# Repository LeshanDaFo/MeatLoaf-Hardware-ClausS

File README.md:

# Meatloaf ESP32-S3 Carrier Board

Hardware designs and ready-to-flash firmware packages for the [Meatloaf](https://github.com/idolpx/meatloaf) project.

Meatloaf is an ESP32-based interface for Commodore computers. It connects to the IEC serial bus and can provide access to disk images, SD-card files, network services, and other Meatloaf firmware features.

This repository contains an independent hardware implementation designed and maintained by Claus Schlereth. The original Meatloaf firmware is developed separately in the upstream Meatloaf repository.

## Available hardware revisions

| Revision | Status | Hardware documentation | Firmware |
| --- | --- | --- | --- |
| PCB v1.0 | Published | [Documentation](Hardware/PCB-v1.0/README.md) · [KiCad files](Hardware/PCB-v1.0/KiCad/) · [Production files](Hardware/PCB-v1.0/Production/) | [Firmware packages](Firmware/v1.0/) · [Installation instructions](Firmware/README.md) |
| PCB v1.1a | Discrete IEC input stages | [Hardware package](Hardware/PCB-v1.1a/README.md) | [SPI3 firmware compatibility](Firmware/v1.1/README.md#spi3-hardware) |
| PCB v1.1b | 74LVC541A IEC input buffer | [Hardware package](Hardware/PCB-v1.1b/README.md) | [SPI3 firmware compatibility](Firmware/v1.1/README.md#spi3-hardware) |
| PCB v1.1c | USB-C power input and plug-in W5500 module | [Hardware package](Hardware/PCB-v1.1c/README.md) | [SPI3 firmware compatibility](Firmware/v1.1/README.md#spi3-hardware) |

Each hardware revision has its own design, documentation, images, and manufacturing files. Files from different revisions must not be mixed.

The table above is the starting point for revision-specific compatibility,
placement, GPIO assignments, schematics, PCB images, KiCad sources, 3D data,
and manufacturing files. The [hardware overview](Hardware/README.md) provides a
revision-independent index of the available design material.

### PCB v1.1a

PCB v1.1a uses discrete BC847BS stages for the IEC inputs.

### PCB v1.1b

PCB v1.1b replaces the discrete IEC input stages of v1.1a with a 74LVC541A
buffer and retains the BC847BS output stages.

### PCB v1.1c

PCB v1.1c adds USB-C power, a plug-in W5500 Mini module and two RGB headers.

## Getting started

### Using an assembled board

1. Identify the PCB revision and the installed ESP32 module configuration.
2. Download the matching firmware package from the appropriate [`Firmware/`](Firmware/) revision directory or from GitHub Releases.
3. Follow the [firmware installation instructions](Firmware/README.md).
4. Verify that all connections are correct before switching on the connected Commodore computer.

### Building the hardware

Before ordering or assembling a PCB:

1. Open the documentation for the required hardware revision.
2. Review its schematic and PCB layout.
3. Make sure all manufacturing files belong to the same revision.
4. Check component availability, footprints, connector orientation, and ESP32-S3 module compatibility.
5. Review the applicable license and third-party notices.

The files under `Production/` are intended for PCB manufacturing and assembly. The editable KiCad project remains the authoritative design source.

## Firmware

[Open the Meatloaf Carrier Webflasher](https://leshandafo.github.io/Meatloaf-Hardware-ClausS/) to install firmware directly from your browser.

Firmware packages are hardware-specific and may also differ by flash capacity,
PSRAM capacity, GPIO assignments, and other board configuration details. A
development-board name or matching connector position alone does not determine
the correct package.

Use the firmware link for the selected hardware revision and follow the
[`Firmware/README.md`](Firmware/README.md) instructions to identify the module
and choose a compatible package. Do not assume that firmware for one revision
or memory configuration is suitable for another.

## Repository structure

```text
.
├── Hardware/
│   ├── README.md
│   ├── PCB-v1.0/
│   │   ├── README.md
│   │   ├── 3D/
│   │   ├── Images/
│   │   ├── KiCad/
│   │   ├── PDF/
│   │   └── Production/
│   ├── PCB-v1.1a/
│   ├── PCB-v1.1b/
│   └── PCB-v1.1c/
│       ├── README.md
│       ├── 3D/
│       ├── Images/
│       ├── KiCad/
│       ├── PDF/
│       └── Production/
├── Firmware/
│   ├── README.md
│   ├── v1.0/
│   └── v1.1/
├── LICENSE.md
└── LIZENZ.md
```

Future published hardware revisions will continue to use separate directories.

## Revision history

| Date | Revision | Summary |
| --- | --- | --- |
| 2026-10-21 | PCB v1.0 | Initial published hardware revision with KiCad sources, schematic PDF, PCB images, 3D assembly, production files, and N8R8/N16R8 firmware packages |
| 2026-11-11 | PCB v1.1a, v1.1b and v1.1c | Dedicated W5500 SPI3 bus, updated KiCad projects, manufacturing files, and 3D assets |

Each hardware revision has its own technical documentation.

## Project status

This is a hobby hardware project under active development.

Features, test status, component choices, and firmware compatibility may differ between hardware revisions. Always consult the documentation for the exact PCB revision instead of assuming that information for another revision also applies.

## License and third-party materials

The original hardware design materials are provided under the project's custom non-commercial hardware license:

- [English translation](LICENSE.md)
- [Verbindliche deutsche Fassung](LIZENZ.md)

Private builds and non-profit group orders at documented actual cost are permitted under the conditions of that license. Commercial use requires separate written permission.

Firmware, KiCad libraries, component models, trademarks, and other third-party materials may be governed by separate licenses or usage conditions. The project license does not grant additional rights to those materials.

## Safety notice

The project is provided for experimentation and hobby use without a guarantee of functionality, electrical safety, regulatory compliance, or fitness for a particular purpose.

Check wiring, connector orientation, supply voltage, component ratings, and the selected hardware revision before powering the board.

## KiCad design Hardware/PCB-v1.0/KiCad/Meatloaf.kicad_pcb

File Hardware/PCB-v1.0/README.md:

# Meatloaf PCB v1.0

This document contains the assembly and connection information specific to
carrier-board revision **PCB v1.0**. Do not apply these details to another PCB
revision without checking its own documentation.

## Compatible ESP32-S3 development boards

The carrier provides one common left-hand socket row and two alternative
right-hand socket rows. It supports the following development-board layouts:

| Development-board layout | Right-hand socket row |
| --- | --- |
| [Espressif ESP32-S3-DevKitC-1](https://docs.espressif.com/projects/esp-dev-kits/en/latest/esp32s3/esp32-s3-devkitc-1/user_guide_v1.1.html) | Inner row |
| [Freenove ESP32-S3 WROOM Board](https://github.com/Freenove/Freenove_ESP32_S3_WROOM_Board) (FNK0085) | Outer row |
| [YD-ESP32-S3 development board](https://github.com/vcc-gnd/YD-ESP32-S3) | Outer row |

The firmware provided for PCB v1.0 uses the microSD-card slot on the carrier
board. Although the Freenove ESP32-S3 WROOM Board has its own microSD-card
slot, that slot is not enabled by this firmware. Insert the microSD card into
the carrier-board slot when using the Freenove board.

The socket row is determined by the board's physical dimensions, header
spacing, and pin assignment. Flash and PSRAM capacity are separate from this
mechanical choice and do not determine which socket row to use.

The named layouts are supported by this design. A different memory
variant or another board from the same product family may fit, but it is not
automatically compatible. Compare its complete pinout, header spacing, and
dimensions with the KiCad design before fitting it.

The PCB silkscreen label `ESP32-S3-DevKitC-1` identifies the development-board
layout, not its memory configuration. Determine the installed module's flash
and PSRAM capacity separately and use the
[firmware instructions](../../Firmware/README.md) to select the correct
firmware package.

## Module placement

1. Disconnect USB, IEC, and every other power source.
2. Place the carrier PCB in front of you with the two IEC connectors on the
   **left** and the status LEDs on the **right**.
3. Select the appropriate right-hand socket row:
   - Espressif ESP32-S3-DevKitC-1: **inner** right-hand socket row.
   - Freenove ESP32-S3 WROOM Board: **outer** right-hand socket row.
   - YD-ESP32-S3: **outer** right-hand socket row.
4. Orient the ESP32-S3 development board so that its USB connector or
   connectors point **downward, toward you**.
5. Carefully insert the module into the common left-hand socket row and the
   selected right-hand socket row on the component side of the carrier.
6. Check both ends of both headers. A one-pin offset will connect the wrong
   signals and may damage the module or carrier.
7. Before applying power, verify the `3V3` and `GND` positions against the
   module's own pinout.

The three placement outlines and their names are printed on the PCB
silkscreen. Fit only one ESP32-S3 board at a time; the two right-hand rows are
alternatives, not two simultaneous connections.

## GPIO usage on PCB v1.0

The following table describes the electrical connections made by the carrier
board. These assignments are taken from the current PCB v1.0 schematic and
layout.

| ESP32-S3 GPIO | Carrier-board function | Schematic net / note |
| ---: | --- | --- |
| 0 | ROOT button `SW1` | Navigates to the root directory of the internal flash filesystem |
| 1 | WiFi status LED `D2` | LED control |
| 2 | Bus status LED `D3` | LED control |
| 4 | IEC ATN | `M_ATN` |
| 5 | IEC CLK input | `M_CLK_IN` |
| 6 | IEC DATA input | `M_DATA_IN` |
| 7 | IEC SRQ | `M_SRQ` |
| 8 | IEC RESET | `M_RST` |
| 11 | microSD MOSI/CMD | `MOSI` |
| 12 | microSD clock | `SCK` |
| 13 | microSD MISO/DAT0 | `MISO` |
| 16 | IEC DATA output | `M_DATA_OUT` |
| 17 | IEC CLK output | `M_CLK_OUT` |
| 46 | microSD chip select | `CS` |

The carrier also connects the module's `3V3` and `GND` pins. The module's
`5V` and `EN`/`CHIP_PU` pins are not connected by PCB v1.0.

IEC CLK and DATA use **separate input and output GPIOs** on this carrier:
GPIO5/GPIO17 for CLK and GPIO6/GPIO16 for DATA. Firmware for PCB v1.0 must use
this split-line arrangement. A generic pin map that assigns both directions to
GPIO5 or both directions to GPIO6 does not match the carrier hardware.

GPIOs not listed above are not connected by the carrier, but they are not
necessarily free for arbitrary use: an installed development board may use
them for its own RGB LED, USB interface, camera connector, or other onboard
hardware. Do not enable a module-local peripheral if it drives a GPIO used in
the table above.

## Firmware selection

Firmware selection depends on the installed module's flash and PSRAM capacity
and must also match the carrier board's GPIO assignments and hardware
configuration. The development-board manufacturer and socket-row position
alone do not determine the correct firmware variant. Refer to the
[firmware instructions](../../Firmware/README.md) before flashing.

## Design and production files

- [Schematic PDF](PDF/Meatloaf-PCB-v1.0-Schematic.pdf)
- [KiCad project](KiCad/)
- [Production files](Production/)
- [PCB images](Images/)
- [Complete STEP assembly](3D/Meatloaf-PCB-v1.0-Assembly.step)

The editable KiCad project is the authoritative source if this document and a
design file ever disagree.

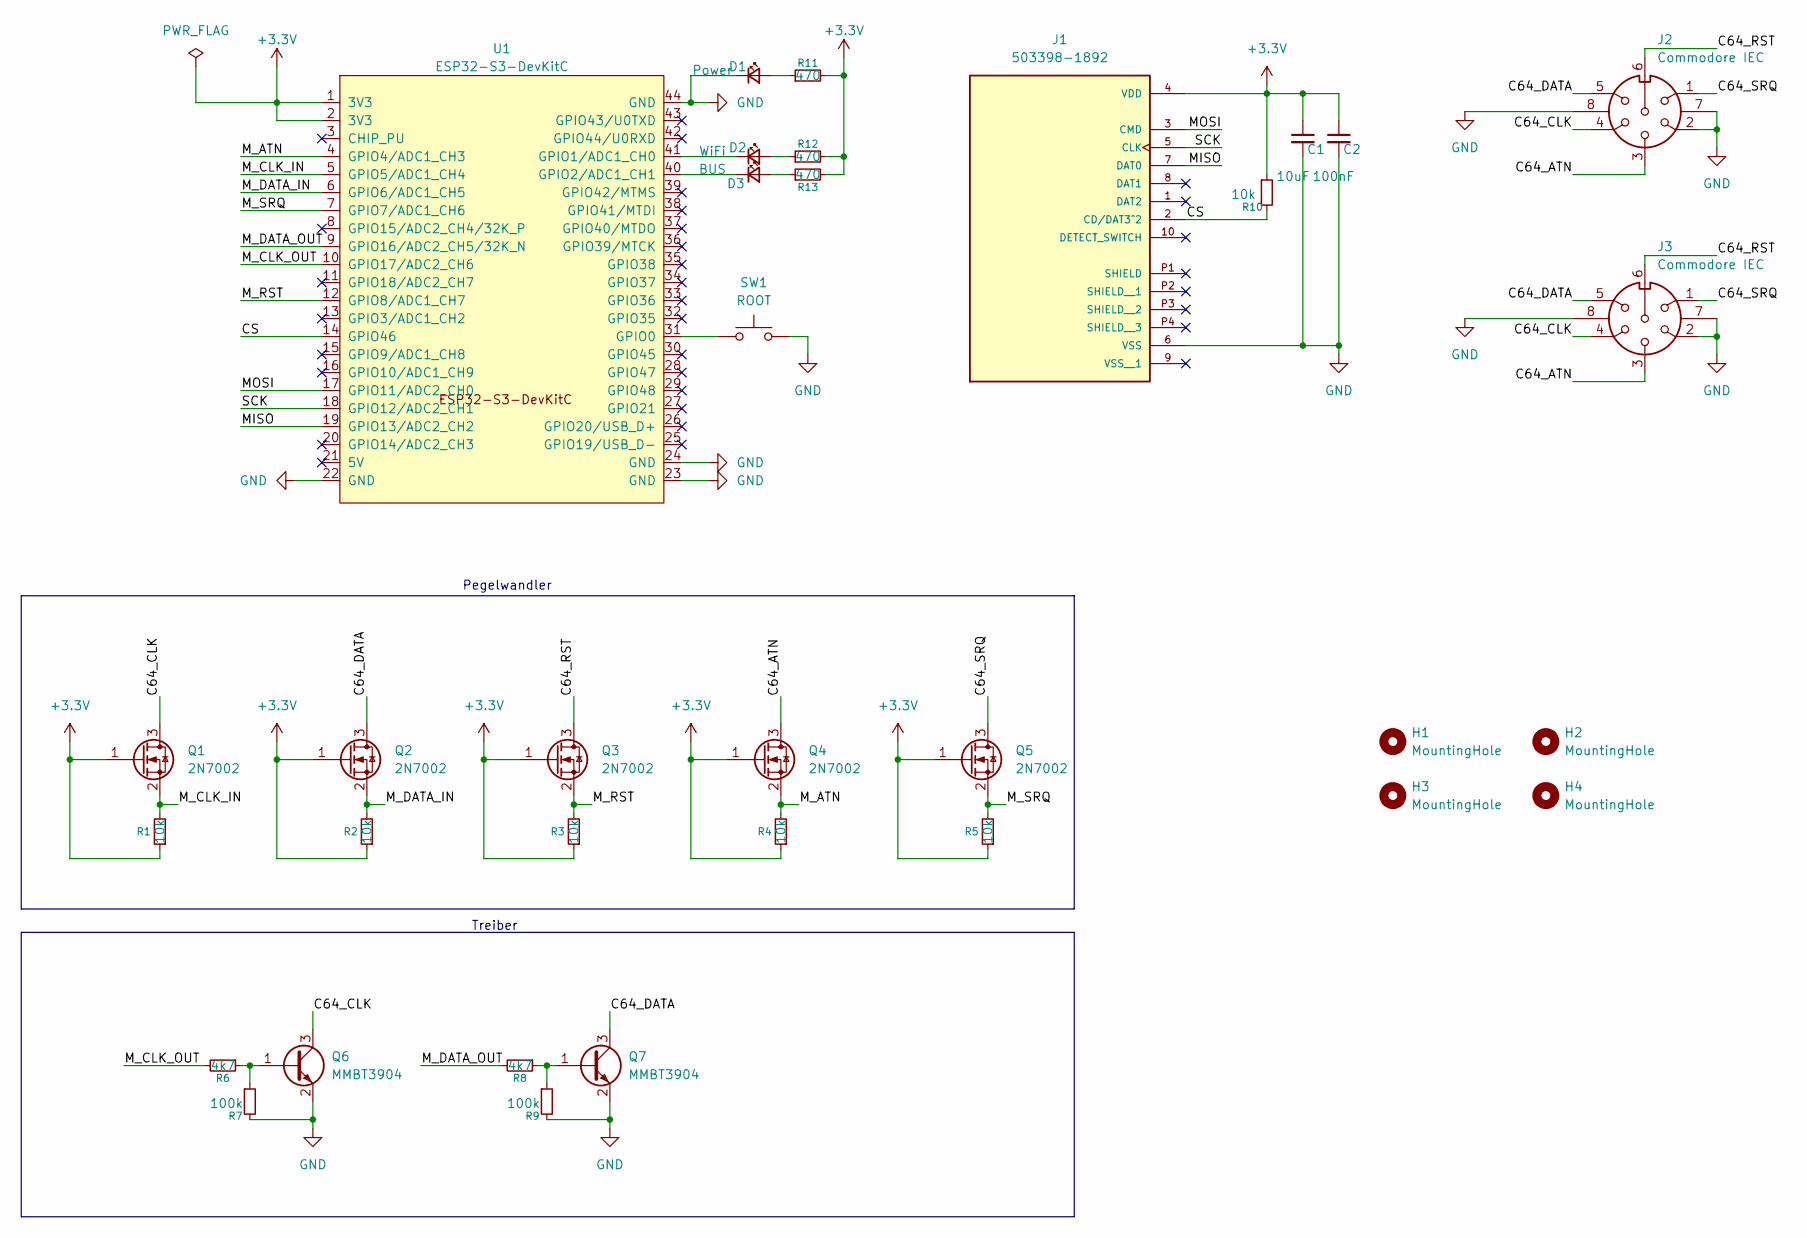
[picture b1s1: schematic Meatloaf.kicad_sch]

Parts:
C1: 10uF; C_0603_1608Metric_Pad1.08x0.95mm_HandSolder
C2: 100nF; C_0603_1608Metric_Pad1.08x0.95mm_HandSolder
D1: Power; LED_D3.0mm
D2: WiFi; LED_D3.0mm
D3: BUS; LED_D3.0mm
H1, H2, H3, H4: MountingHole; MountingHole_3.2mm_M3
J1: 503398-1892; MOLEX_503398-1892; PARTREV 0; LCSC Part # C428492
J2, J3: Commodore IEC; Commodore_IEC; MPN 0105 06
Q1, Q2, Q3, Q4, Q5: 2N7002; SOT-23; LCSC Part # C8545
Q6, Q7: MMBT3904; SOT-23; LCSC Part # C20526
R1, R2, R3, R4, R5, R10: 10k; R_0603_1608Metric_Pad0.98x0.95mm_HandSolder
R6, R8: 4k7; R_0603_1608Metric_Pad0.98x0.95mm_HandSolder
R7, R9: 100k; R_0603_1608Metric_Pad0.98x0.95mm_HandSolder
R11, R12, R13: 470; R_Axial_DIN0207_L6.3mm_D2.5mm_P10.16mm_Horizontal
SW1: ROOT; SW_Tactile_SPST_Angled_PTS645Vx58-2LFS
U1: ESP32-S3-DevKitC; ESP32-S3-DevKitC-1

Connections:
+3.3V: C1.1, C2.1, J1.4 (VDD), Q1.1 (G), Q2.1 (G), Q3.1 (G), Q4.1 (G), Q5.1 (G), R1.1, R2.1, R3.1, R4.1, R5.1, R10.1, R11.2, R12.2, R13.2, U1.1 (3V3), U1.2 (3V3)
/C64_ATN: J2.3, J3.3, Q4.3 (D)
/C64_CLK: J2.4, J3.4, Q1.3 (D), Q6.3 (C)
/C64_DATA: J2.5, J3.5, Q2.3 (D), Q7.3 (C)
/C64_RST: J2.6, J3.6, Q3.3 (D)
/C64_SRQ: J2.1, J3.1, Q5.3 (D)
/CS: J1.2 (CD/DAT3^2), R10.2, U1.14 (GPIO46)
/MISO: J1.7 (DAT0), U1.19 (GPIO13/ADC2_CH2)
/MOSI: J1.3 (CMD), U1.17 (GPIO11/ADC2_CH0)
/M_ATN: Q4.2 (S), R4.2, U1.4 (GPIO4/ADC1_CH3)
/M_CLK_IN: Q1.2 (S), R1.2, U1.5 (GPIO5/ADC1_CH4)
/M_CLK_OUT: R6.2, U1.10 (GPIO17/ADC2_CH6)
/M_DATA_IN: Q2.2 (S), R2.2, U1.6 (GPIO6/ADC1_CH5)
/M_DATA_OUT: R8.2, U1.9 (GPIO16/ADC2_CH5/32K_N)
/M_RST: Q3.2 (S), R3.2, U1.12 (GPIO8/ADC1_CH7)
/M_SRQ: Q5.2 (S), R5.2, U1.7 (GPIO7/ADC1_CH6)
/SCK: J1.5 (CLK), U1.18 (GPIO12/ADC2_CH1)
GND: C1.2, C2.2, D1.1 (K), J1.6 (VSS), J2.2, J2.7, J2.8, J3.2, J3.7, J3.8, Q6.2 (E), Q7.2 (E), R7.2, R9.2, SW1.2, U1.22 (GND), U1.23 (GND), U1.24 (GND), U1.44 (GND)
unnamed: D1.2 (A), R11.1
unnamed: D2.2 (A), R12.1
unnamed: D2.1 (K), U1.41 (GPIO1/ADC1_CH0)
unnamed: D3.2 (A), R13.1
unnamed: D3.1 (K), U1.40 (GPIO2/ADC1_CH1)
unnamed: Q6.1 (B), R6.1, R7.1
unnamed: Q7.1 (B), R8.1, R9.1
unnamed: SW1.1, U1.31 (GPIO0)

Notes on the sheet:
Pegelwandler
Treiber

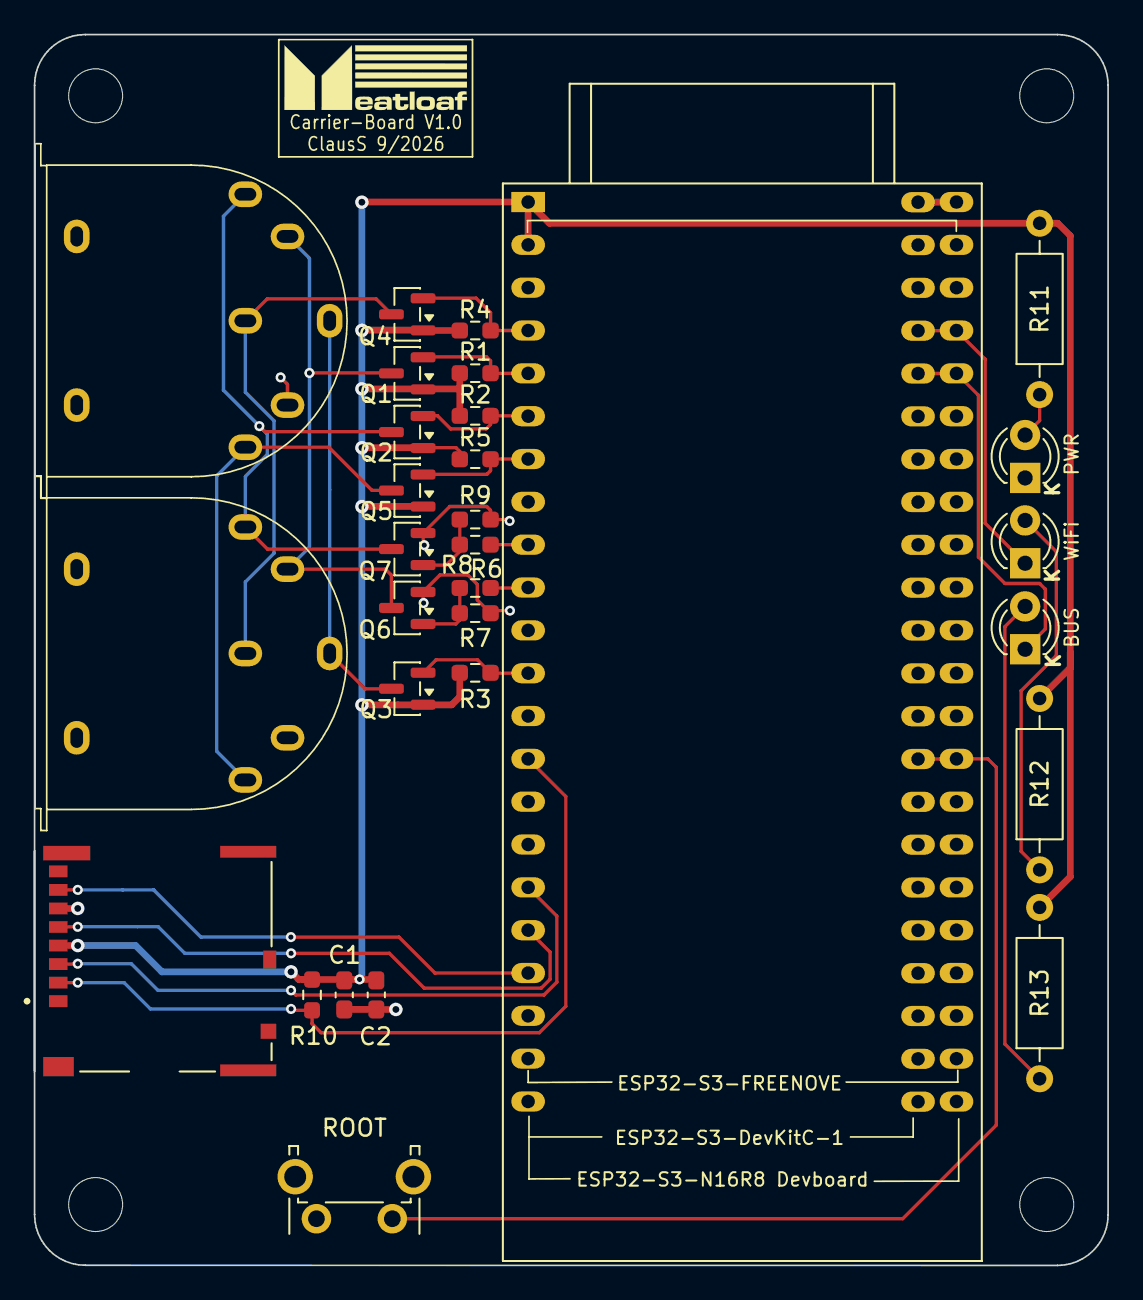
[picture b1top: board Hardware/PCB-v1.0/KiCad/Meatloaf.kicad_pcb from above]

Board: 2 copper layers, 63.7 x 73.0 mm, 34 parts (0 on the bottom side), 26 nets.

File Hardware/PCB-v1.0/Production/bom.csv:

Designator,Footprint,Quantity,Value,LCSC Part #
C1,0603,1,10uF,
C2,0603,1,100nF,
D1,LED_D3.0mm,1,Power,
D2,LED_D3.0mm,1,WiFi,
D3,LED_D3.0mm,1,BUS,
J1,MOLEX_503398-1892,1,503398-1892,C428492
"J2, J3",Commodore_IEC,2,Commodore IEC,0105 06
"Q1, Q2, Q3, Q4, Q5",SOT-23,5,2N7002,C8545
"Q6, Q7",SOT-23,2,MMBT3904,C20526
"R1, R10, R2, R3, R4, R5",0603,6,10k,
"R11, R12, R13",R_Axial_DIN0207_L6.3mm_D2.5mm_P10.16mm_Horizontal,3,470,
"R6, R8",0603,2,4k7,
"R7, R9",0603,2,100k,
SW1,SW_Tactile_SPST_Angled_PTS645Vx58-2LFS,1,ROOT,
U1,ESP32-S3-DevKitC-1,1,ESP32-S3-DevKitC,

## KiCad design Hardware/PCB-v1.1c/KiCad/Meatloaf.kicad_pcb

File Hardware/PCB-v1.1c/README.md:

# Meatloaf PCB v1.1c

PCB v1.1c retains the 74LVC541A IEC input buffer and BC847BS
open-collector output stages of v1.1b. It adds a USB-C power input,
a footprint for a 12-pin W5500 Mini Ethernet module, and two RGB headers.

## Power and connections

- P1 is a 5 V USB-C power input. CC1 and CC2 each have a 5.1 kΩ pull-down.
  VBUS connects directly to the ESP32 module's 5 V rail. D4 (PESD5V0S1BA)
  is on this rail. F1 (20 V / 2 A in the BOM) feeds the RGB branch.
  Check the power path before connecting both carrier and module USB power.
- P4 is the W5500 Mini module footprint. Its 3.3 V pins are 8 and 9,
  with GND on 1, 2 and 7. SPI3 MOSI (GPIO41) is on pin 3, SCK (GPIO39)
  on pin 4 and MISO (GPIO40) on pin 12. CS (GPIO10) is on pin 5 and
  INT (GPIO9) on pin 6. Pin 11 (RST) has no carrier connection to an ESP32 GPIO.
  Verify the module's pinout and orientation before fitting it.
- J1 and J2 share the same non-inverting 5 V data signal from GPIO48
  through Q4 and R19–R22. Both headers use pin 1 for data, pin 2 for
  fused +5 V and pin 3 for GND. Both receive the same LED data stream.
- J3 and J4 carry IEC. J5 is the microSD socket.

## Firmware

The IEC, SD, W5500 and RGB GPIO assignments match the
[common v1.1 pin map](../PCB-v1.1a/README.md#gpio-assignments). See
[v1.1 firmware compatibility](../../Firmware/v1.1/README.md#spi3-hardware).

## Design files

- [KiCad project](KiCad/Meatloaf.kicad_pro)
- [STEP assembly](3D/Meatloaf-PCB-v1.1c-Assembly.step)
- [Manufacturing files](Production/)
- [Component datasheets](PDF/)

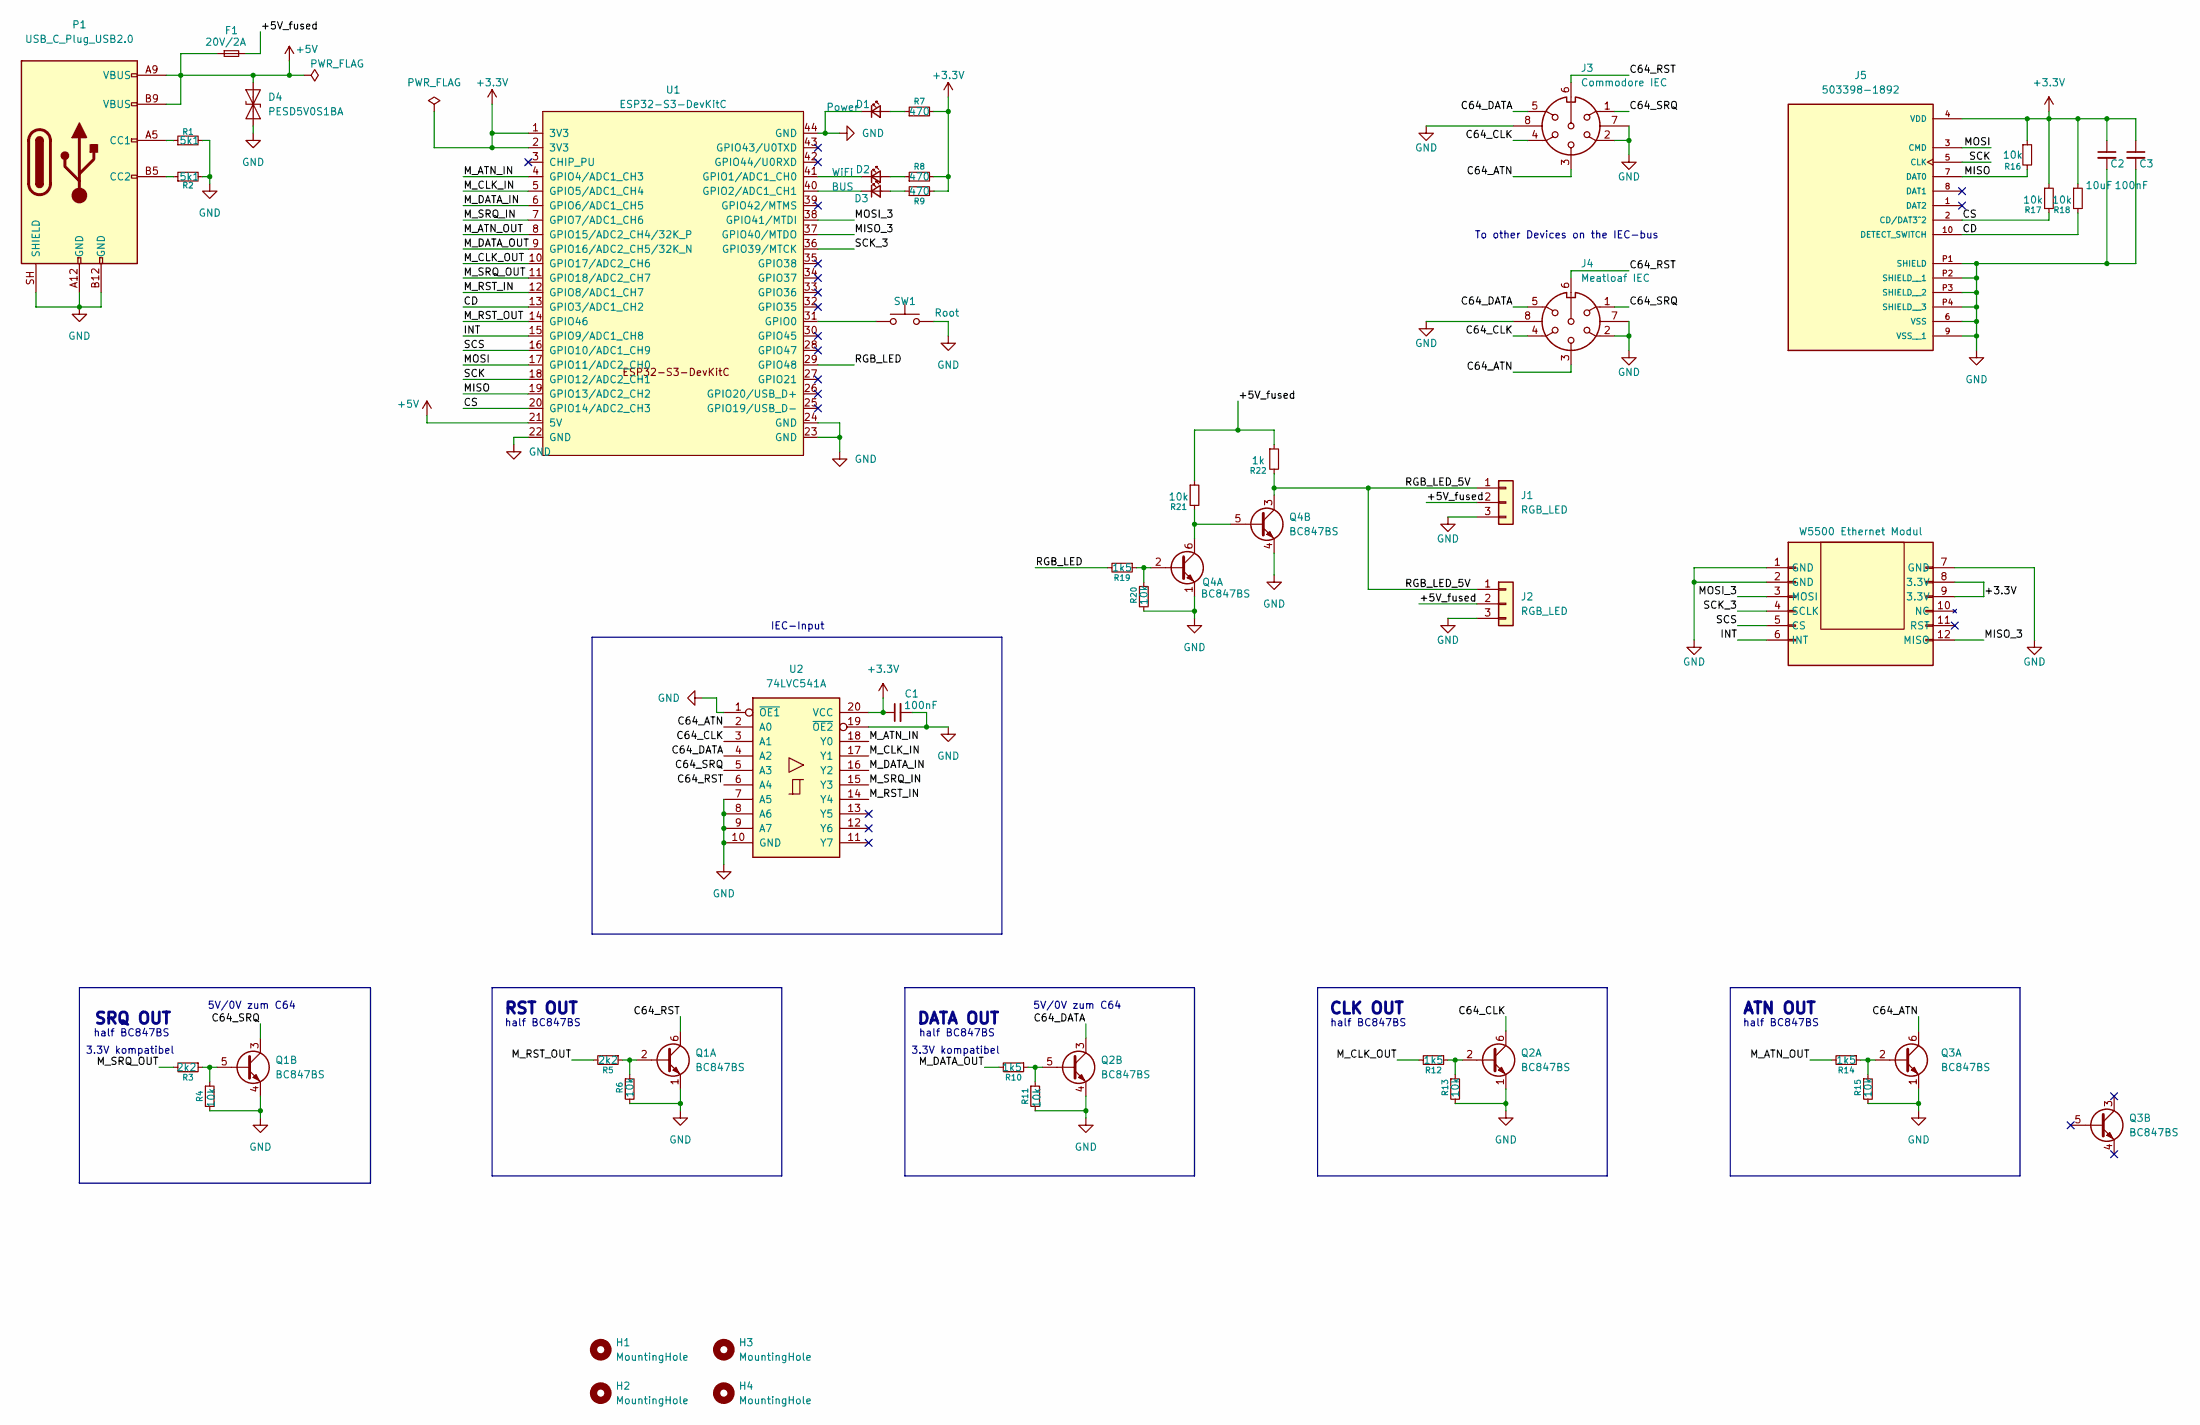
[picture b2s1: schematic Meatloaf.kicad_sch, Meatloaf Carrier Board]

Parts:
C1: 100nF; C_0603_1608Metric_Pad1.08x0.95mm_HandSolder
C2: 10uF; C_0603_1608Metric
C3: 100nF; C_0603_1608Metric
D1: Power; LED_D3.0mm
D2: WiFi; LED_D3.0mm
D3: BUS; LED_D3.0mm
D4: PESD5V0S1BA; D_SOD-323
F1: 20V/2A; Fuse_1206_3216Metric
H1, H2, H3, H4: MountingHole; MountingHole_3.2mm_M3
J1, J2: RGB_LED; PinHeader_1x03_P2.54mm_Vertical
J3: Commodore IEC; Commodore_IEC; MPN 0105 06
J4: Meatloaf IEC; Commodore_IEC; MPN 0105 06
J5: 503398-1892; MOLEX_503398-1892; PARTREV 0; LCSC Part # C428492
P1: USB_C_Plug_USB2.0; USB_C_Receptacle_GCT_USB4125-xx-x_6P_TopMnt_Horizontal; JLCPCB Part# C309366
P4: W5500 Ethernet Modul; W5500 Ethernet Modul 12pin
Q1, Q2, Q3, Q4: BC847BS; SOT-363_SC-70-6
R1, R2: 5k1; R_0603_1608Metric
R3, R5: 2k2; R_0402_1005Metric
R4, R6, R11, R13, R15, R16, R17, R18, R20, R21: 10k; R_0402_1005Metric
R7, R8, R9: 470; R_Axial_DIN0207_L6.3mm_D2.5mm_P10.16mm_Horizontal
R10, R12, R14, R19: 1k5; R_0402_1005Metric
R22: 1k; R_0402_1005Metric
SW1: Root; SW_Tactile_SPST_Angled_PTS645Vx39-2LFS
U1: ESP32-S3-DevKitC; ESP32-S3-DevKitC-1
U2: 74LVC541A; TSSOP-20_4.4x6.5mm_P0.65mm; LCSC Part# C53552927

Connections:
+3.3V: C1.1, C2.1, C3.1, J5.4 (VDD), P4.8 (3.3V), P4.9 (3.3V), R7.2, R8.2, R9.2, R16.1, R17.1, R18.1, U1.1 (3V3), U1.2 (3V3), U2.20 (VCC)
+5V: D4.2 (A2), F1.1, P1.A9 (VBUS), P1.B9 (VBUS), U1.21 (5V)
/+5V_fused: F1.2, J1.2, J2.2, R21.1, R22.1
/C64_ATN: J3.3, J4.3, Q3.6 (C1), U2.2 (A0)
/C64_CLK: J3.4, J4.4, Q2.6 (C1), U2.3 (A1)
/C64_DATA: J3.5, J4.5, Q2.3 (C2), U2.4 (A2)
/C64_RST: J3.6, J4.6, Q1.6 (C1), U2.6 (A4)
/C64_SRQ: J3.1, J4.1, Q1.3 (C2), U2.5 (A3)
/CD: J5.10 (DETECT_SWITCH), R18.2, U1.13 (GPIO3/ADC1_CH2)
/CS: J5.2 (CD/DAT3^2), R17.2, U1.20 (GPIO14/ADC2_CH3)
/INT: P4.6 (INT), U1.15 (GPIO9/ADC1_CH8)
/MISO: J5.7 (DAT0), R16.2, U1.19 (GPIO13/ADC2_CH2)
/MISO_3: P4.12 (MISO), U1.37 (GPIO40/MTDO)
/MOSI: J5.3 (CMD), U1.17 (GPIO11/ADC2_CH0)
/MOSI_3: P4.3 (MOSI), U1.38 (GPIO41/MTDI)
/M_ATN_IN: U1.4 (GPIO4/ADC1_CH3), U2.18 (Y0)
/M_ATN_OUT: R14.2, U1.8 (GPIO15/ADC2_CH4/32K_P)
/M_CLK_IN: U1.5 (GPIO5/ADC1_CH4), U2.17 (Y1)
/M_CLK_OUT: R12.2, U1.10 (GPIO17/ADC2_CH6)
/M_DATA_IN: U1.6 (GPIO6/ADC1_CH5), U2.16 (Y2)
/M_DATA_OUT: R10.2, U1.9 (GPIO16/ADC2_CH5/32K_N)
/M_RST_IN: U1.12 (GPIO8/ADC1_CH7), U2.14 (Y4)
/M_RST_OUT: R5.2, U1.14 (GPIO46)
/M_SRQ_IN: U1.7 (GPIO7/ADC1_CH6), U2.15 (Y3)
/M_SRQ_OUT: R3.2, U1.11 (GPIO18/ADC2_CH7)
/RGB_LED: R19.2, U1.29 (GPIO48)
/RGB_LED_5V: J1.1, J2.1, Q4.3 (C2), R22.2
/SCK: J5.5 (CLK), U1.18 (GPIO12/ADC2_CH1)
/SCK_3: P4.4 (SCLK), U1.36 (GPIO39/MTCK)
/SCS: P4.5 (CS), U1.16 (GPIO10/ADC1_CH9)
GND: C1.2, C2.2, C3.2, D1.1 (K), D4.1 (A1), J1.3, J2.3, J3.2, J3.7, J3.8, J4.2, J4.7, J4.8, J5.6 (VSS), J5.9 (VSS__1), J5.P1 (SHIELD), J5.P2 (SHIELD__1), J5.P3 (SHIELD__2), J5.P4 (SHIELD__3), P1.A12 (GND), P1.B12 (GND), P1.SH (SHIELD), P4.1 (GND), P4.2 (GND), P4.7 (GND), Q1.1 (E1), Q1.4 (E2), Q2.1 (E1), Q2.4 (E2), Q3.1 (E1), Q4.1 (E1), Q4.4 (E2), R1.2, R2.2, R4.2, R6.2, R11.2, R13.2, R15.2, R20.2, SW1.2, U1.22 (GND), U1.23 (GND), U1.24 (GND), U1.44 (GND), U2.1 (~OE1), U2.7 (A5), U2.8 (A6), U2.9 (A7), U2.10 (GND), U2.19 (~OE2)
unnamed: D1.2 (A), R7.1
unnamed: D2.2 (A), R8.1
unnamed: D2.1 (K), U1.41 (GPIO1/ADC1_CH0)
unnamed: D3.2 (A), R9.1
unnamed: D3.1 (K), U1.40 (GPIO2/ADC1_CH1)
unnamed: P1.A5 (CC1), R1.1
unnamed: P1.B5 (CC2), R2.1
unnamed: Q1.2 (B1), R5.1, R6.1
unnamed: Q1.5 (B2), R3.1, R4.1
unnamed: Q2.2 (B1), R12.1, R13.1
unnamed: Q2.5 (B2), R10.1, R11.1
unnamed: Q3.2 (B1), R14.1, R15.1
unnamed: Q4.2 (B1), R19.1, R20.1
unnamed: Q4.5 (B2), Q4.6 (C1), R21.2
unnamed: SW1.1, U1.31 (GPIO0)

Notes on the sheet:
half BC847BS
CLK OUT
RST OUT
3.3V kompatibel
5V/0V zum C64
ATN OUT
IEC-Input
DATA OUT
To other Devices on the IEC-bus
SRQ OUT

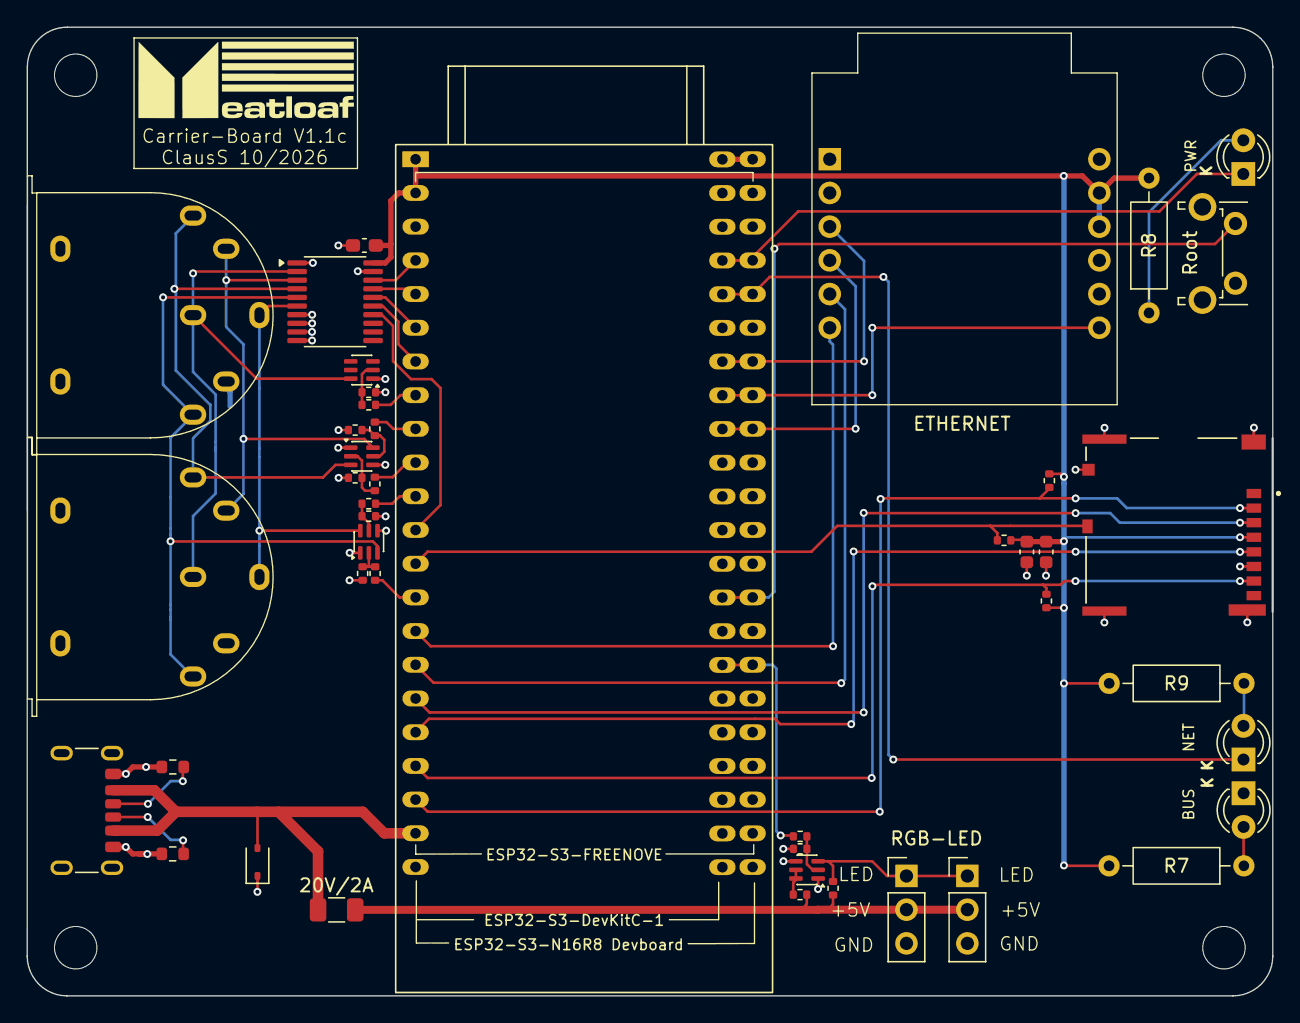
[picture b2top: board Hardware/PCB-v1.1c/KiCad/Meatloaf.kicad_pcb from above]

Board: 2 copper layers, 93.9 x 73.0 mm, 48 parts (0 on the bottom side), 46 nets.

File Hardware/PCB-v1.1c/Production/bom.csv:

Designator,Footprint,Quantity,Value,LCSC Part #
"C1, C3",0603,2,100nF,
C2,0603,1,10uF,
F1,1206,1,20V/2A,
J5,MOLEX_503398-1892,1,503398-1892,C428492
P1,USB_C_Receptacle_GCT_USB4125-xx-x_6P_TopMnt_Horizontal,1,USB_C_Plug_USB2.0,
"Q1, Q2, Q3, Q4",SOT-363_SC-70-6,4,BC847BS,
"R1, R2",0603,2,5k1,
"R10, R12, R14, R19",0402,4,1k5,
"R11, R13, R15, R16, R17, R18, R20, R21, R4, R6",0402,10,10k,
R22,0402,1,1k,
"R3, R5",0402,2,2k2,
SW1,SW_Tactile_SPST_Angled_PTS645Vx39-2LFS,1,Root,
U1,ESP32-S3-DevKitC-1,1,ESP32-S3-DevKitC,
U2,TSSOP-20_4.4x6.5mm_P0.65mm,1,74LVC541A,

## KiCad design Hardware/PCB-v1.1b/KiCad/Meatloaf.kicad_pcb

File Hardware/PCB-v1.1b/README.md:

# Meatloaf PCB v1.1b

PCB v1.1b replaces the discrete IEC input stages of [v1.1a](../PCB-v1.1a/README.md)
with a 74LVC541A buffer. It retains the BC847BS open-collector output stages,
the W5500 header and the 5 V RGB data level shifter.

The rendering and STEP assembly include the female socket strips beneath the
ESP32-S3 development board so that its installed height is represented.

## IEC input buffer

The 74LVC541A buffers ATN, CLK, DATA, SRQ and RESET without inverting them.
The IEC output stages retain their existing polarity. The
[GPIO assignments](../PCB-v1.1a/README.md#gpio-assignments),
[W5500 connector](../PCB-v1.1a/README.md#ethernet-connector), and
[RGB connector](../PCB-v1.1a/README.md#addressable-rgb-led-connector)
are shared with v1.1a.

## Directory contents

- [`3D/Meatloaf-PCB-v1.1b-Assembly.step`](3D/Meatloaf-PCB-v1.1b-Assembly.step)
  is the complete mechanical STEP assembly exported from the v1.1b PCB.
- [`KiCad/`](KiCad/) contains the editable schematic, PCB, project file,
  project libraries, and the local 3D models referenced by the PCB.
- [`Images/`](Images/) contains the verified KiCad rendering.
- [`PDF/`](PDF/) contains the retained component documentation for the Molex
  503398-1892 microSD connector, the 74LVC541A input buffer, and the BC847BS
  dual transistors used by the design.
- [`Production/`](Production/) contains the current Gerber/drill archive,
  BOM, position data, designator data, and IPC netlist.

The KiCad project is the authoritative design source. Before ordering boards,
inspect the Gerber archive and placement data in independent viewers and make
sure every file belongs to revision v1.1b.

## Firmware

PCB v1.1b uses the common v1.1 configuration with split IEC lines,
SD Card Detect on GPIO3, SD chip select on GPIO14 and a dedicated W5500 SPI3 bus.
See [v1.1 firmware compatibility](../../Firmware/v1.1/README.md#spi3-hardware).

## Physical prototype validation

The assembled PCB v1.1b prototype was tested with no fault detected in the
following areas before the 2026-11-01 +5 V routing update:

1. IEC operation with normal and accelerated transfers, including loading,
   timing, and signal levels.
2. SD-card insertion and removal while Ethernet was active.
3. W5500 module pinout, startup behavior, and sustained network operation.
4. 3.3 V rail minimum and regulator temperature under combined WiFi,
   Ethernet, SD-write, and RGB load.
5. Connector orientation, microSD insertion clearance, button access, and
   enclosure fit.

## Third-party material

The project contains third-party footprints, symbols, models, and component
documentation. Their original license and attribution files remain with the
corresponding material. The repository's project license does not replace
those third-party terms.

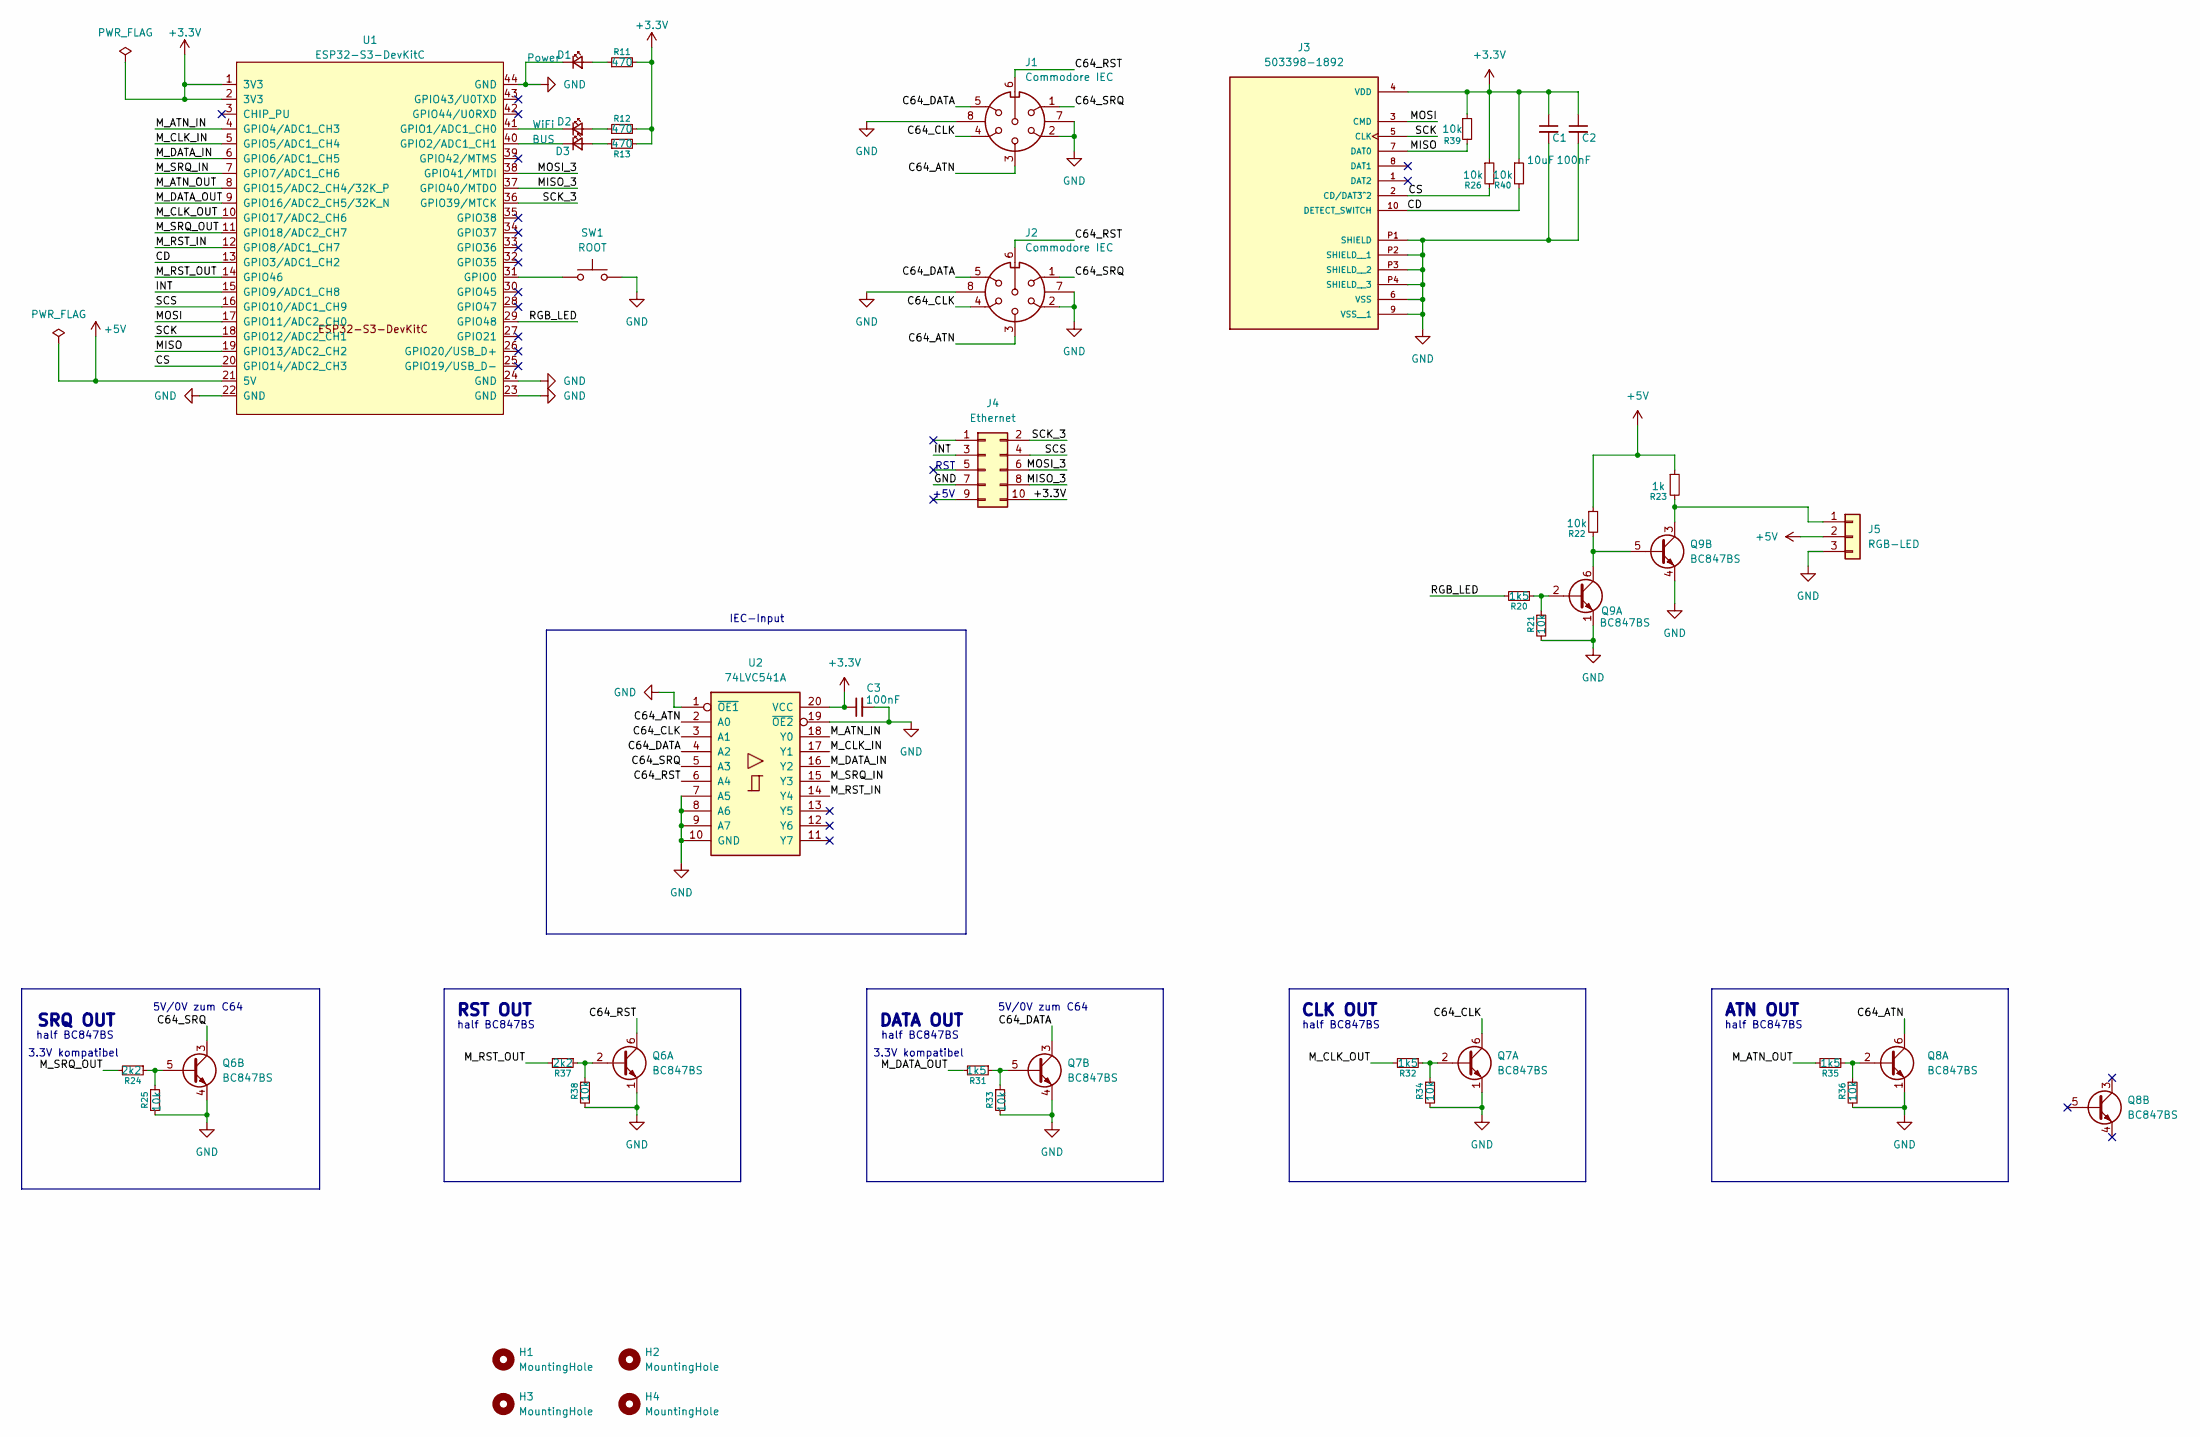
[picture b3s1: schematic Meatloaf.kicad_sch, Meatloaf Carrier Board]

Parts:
C1: 10uF; C_0603_1608Metric
C2: 100nF; C_0603_1608Metric
C3: 100nF; C_0603_1608Metric_Pad1.08x0.95mm_HandSolder
D1: Power; LED_D3.0mm
D2: WiFi; LED_D3.0mm
D3: BUS; LED_D3.0mm
H1, H2, H3, H4: MountingHole; MountingHole_3.2mm_M3
J1, J2: Commodore IEC; Commodore_IEC; MPN 0105 06
J3: 503398-1892; MOLEX_503398-1892; PARTREV 0; LCSC Part # C428492
J4: Ethernet; PinHeader_2x05_P2.54mm_Vertical
J5: RGB-LED; PinHeader_1x03_P2.54mm_Vertical
Q6, Q7, Q8, Q9: BC847BS; SOT-363_SC-70-6
R11, R12, R13: 470; R_Axial_DIN0207_L6.3mm_D2.5mm_P10.16mm_Horizontal
R20, R31, R32, R35: 1k5; R_0402_1005Metric
R21, R22, R25, R26, R33, R34, R36, R38, R39, R40: 10k; R_0402_1005Metric
R23: 1k; R_0402_1005Metric
R24, R37: 2k2; R_0402_1005Metric
SW1: ROOT; SW_Tactile_SPST_Angled_PTS645Vx58-2LFS
U1: ESP32-S3-DevKitC; ESP32-S3-DevKitC-1
U2: 74LVC541A; TSSOP-20_4.4x6.5mm_P0.65mm; LCSC Part# C53552927

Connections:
+3.3V: C1.1, C2.1, C3.1, J3.4 (VDD), J4.10, R11.2, R12.2, R13.2, R26.1, R39.1, R40.1, U1.1 (3V3), U1.2 (3V3), U2.20 (VCC)
+5V: J5.2, R22.1, R23.1, U1.21 (5V)
/C64_ATN: J1.3, J2.3, Q8.6 (C1), U2.2 (A0)
/C64_CLK: J1.4, J2.4, Q7.6 (C1), U2.3 (A1)
/C64_DATA: J1.5, J2.5, Q7.3 (C2), U2.4 (A2)
/C64_RST: J1.6, J2.6, Q6.6 (C1), U2.6 (A4)
/C64_SRQ: J1.1, J2.1, Q6.3 (C2), U2.5 (A3)
/CD: J3.10 (DETECT_SWITCH), R40.2, U1.13 (GPIO3/ADC1_CH2)
/CS: J3.2 (CD/DAT3^2), R26.2, U1.20 (GPIO14/ADC2_CH3)
/INT: J4.3, U1.15 (GPIO9/ADC1_CH8)
/MISO: J3.7 (DAT0), R39.2, U1.19 (GPIO13/ADC2_CH2)
/MISO_3: J4.8, U1.37 (GPIO40/MTDO)
/MOSI: J3.3 (CMD), U1.17 (GPIO11/ADC2_CH0)
/MOSI_3: J4.6, U1.38 (GPIO41/MTDI)
/M_ATN_IN: U1.4 (GPIO4/ADC1_CH3), U2.18 (Y0)
/M_ATN_OUT: R35.2, U1.8 (GPIO15/ADC2_CH4/32K_P)
/M_CLK_IN: U1.5 (GPIO5/ADC1_CH4), U2.17 (Y1)
/M_CLK_OUT: R32.2, U1.10 (GPIO17/ADC2_CH6)
/M_DATA_IN: U1.6 (GPIO6/ADC1_CH5), U2.16 (Y2)
/M_DATA_OUT: R31.2, U1.9 (GPIO16/ADC2_CH5/32K_N)
/M_RST_IN: U1.12 (GPIO8/ADC1_CH7), U2.14 (Y4)
/M_RST_OUT: R37.2, U1.14 (GPIO46)
/M_SRQ_IN: U1.7 (GPIO7/ADC1_CH6), U2.15 (Y3)
/M_SRQ_OUT: R24.2, U1.11 (GPIO18/ADC2_CH7)
/RGB_LED: R20.2, U1.29 (GPIO48)
/SCK: J3.5 (CLK), U1.18 (GPIO12/ADC2_CH1)
/SCK_3: J4.2, U1.36 (GPIO39/MTCK)
/SCS: J4.4, U1.16 (GPIO10/ADC1_CH9)
GND: C1.2, C2.2, C3.2, D1.1 (K), J1.2, J1.7, J1.8, J2.2, J2.7, J2.8, J3.6 (VSS), J3.9 (VSS__1), J3.P1 (SHIELD), J3.P2 (SHIELD__1), J3.P3 (SHIELD__2), J3.P4 (SHIELD__3), J4.7, J5.3, Q6.1 (E1), Q6.4 (E2), Q7.1 (E1), Q7.4 (E2), Q8.1 (E1), Q9.1 (E1), Q9.4 (E2), R21.2, R25.2, R33.2, R34.2, R36.2, R38.2, SW1.2, U1.22 (GND), U1.23 (GND), U1.24 (GND), U1.44 (GND), U2.1 (~OE1), U2.7 (A5), U2.8 (A6), U2.9 (A7), U2.10 (GND), U2.19 (~OE2)
unnamed: D1.2 (A), R11.1
unnamed: D2.2 (A), R12.1
unnamed: D2.1 (K), U1.41 (GPIO1/ADC1_CH0)
unnamed: D3.2 (A), R13.1
unnamed: D3.1 (K), U1.40 (GPIO2/ADC1_CH1)
unnamed: J5.1, Q9.3 (C2), R23.2
unnamed: Q6.2 (B1), R37.1, R38.1
unnamed: Q6.5 (B2), R24.1, R25.1
unnamed: Q7.2 (B1), R32.1, R34.1
unnamed: Q7.5 (B2), R31.1, R33.1
unnamed: Q8.2 (B1), R35.1, R36.1
unnamed: Q9.2 (B1), R20.1, R21.1
unnamed: Q9.5 (B2), Q9.6 (C1), R22.2
unnamed: SW1.1, U1.31 (GPIO0)

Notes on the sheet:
half BC847BS
3.3V kompatibel
DATA OUT
5V/0V zum C64
RST OUT
ATN OUT
SRQ OUT
IEC-Input
CLK OUT
RST
+5V
